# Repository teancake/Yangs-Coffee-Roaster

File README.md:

# Yangs-Coffee-Roaster
The shcematic and PCB design of the circuit board used in Yangs' Coffee Roaster.

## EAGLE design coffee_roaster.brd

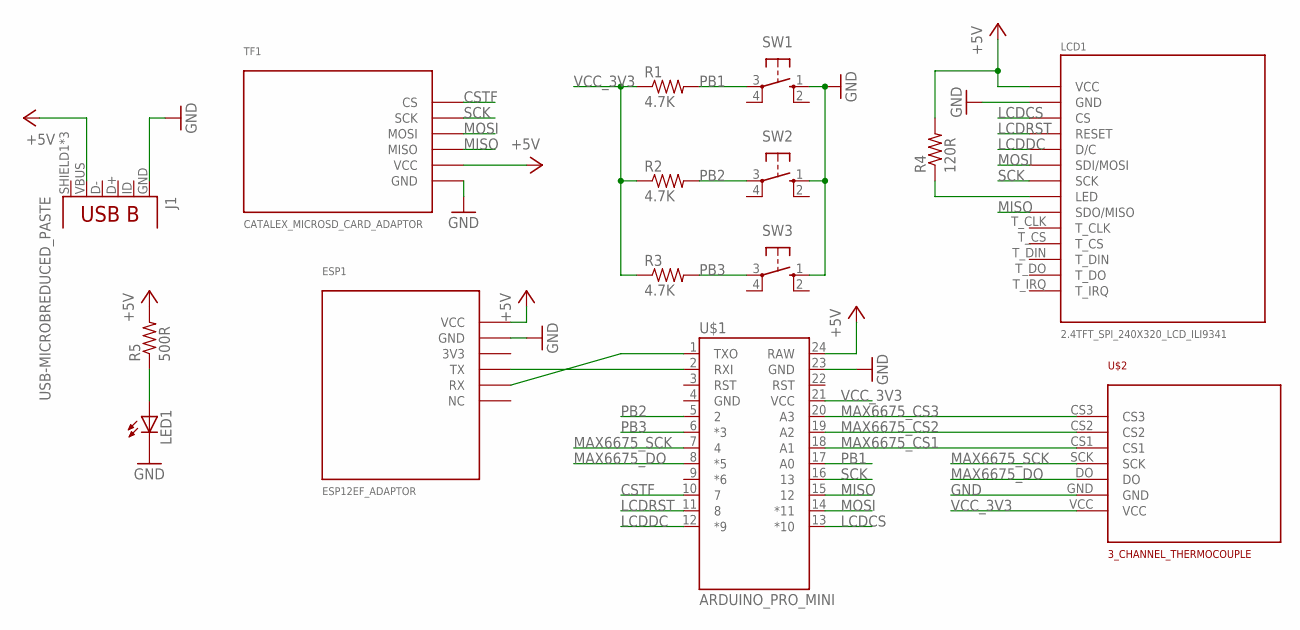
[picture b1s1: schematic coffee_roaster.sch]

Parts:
ESP1: ESP12EF_ADAPTOR
J1: USB-MICROBREDUCED_PASTE; USB-B-MICRO-SMD_V03_RED_PASTE
LCD1: 2.4TFT_SPI_240X320_LCD_ILI9341
LED1: LED5MM
R1, R2, R3: 4.7K; 0603-RES
R4: 120R; 0603-RES
R5: 500R; 0603-RES
SW1, SW2, SW3: PUSHBUTTON; B3F-10XX
TF1: CATALEX_MICROSD_CARD_ADAPTOR
U$1: ARDUINO_PRO_MINI
U$2: 3_CHANNEL_THERMOCOUPLE

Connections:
+5V: ESP1.VCC, J1.VBUS, LCD1.VCC, R4.2, R5.2, TF1.VCC, U$1.24 (RAW)
CSTF: TF1.CS, U$1.10 (7)
GND: ESP1.GND, J1.GND, LCD1.GND, LED1.K (C), SW1.1 (S), SW2.1 (S), SW3.1 (S), TF1.GND, U$1.23 (GND), U$2.GND
LCDCS: LCD1.CS, U$1.13 (*10)
LCDDC: LCD1.D/C, U$1.12 (*9)
LCDRST: LCD1.RESET, U$1.11 (8)
MAX6675_CS1: U$1.18 (A1), U$2.CS1
MAX6675_CS2: U$1.19 (A2), U$2.CS2
MAX6675_CS3: U$1.20 (A3), U$2.CS3
MAX6675_DO: U$1.8 (*5), U$2.DO
MAX6675_SCK: U$1.7 (4), U$2.SCK
MISO: LCD1.SDO/MISO, TF1.MISO, U$1.15 (12)
MOSI: LCD1.SDI/MOSI, TF1.MOSI, U$1.14 (*11)
unnamed: LCD1.LED, R4.1
unnamed: LED1.A, R5.1
unnamed: ESP1.RX, U$1.1 (TXO)
unnamed: ESP1.TX, U$1.2 (RXI)
PB1: R1.2, SW1.3, U$1.17 (A0)
PB2: R2.2, SW2.3, U$1.5 (2)
PB3: R3.2, SW3.3, U$1.6 (*3)
SCK: LCD1.SCK, TF1.SCK, U$1.16 (13)
VCC_3V3: R1.1, R2.1, R3.1, U$1.21 (VCC), U$2.VCC

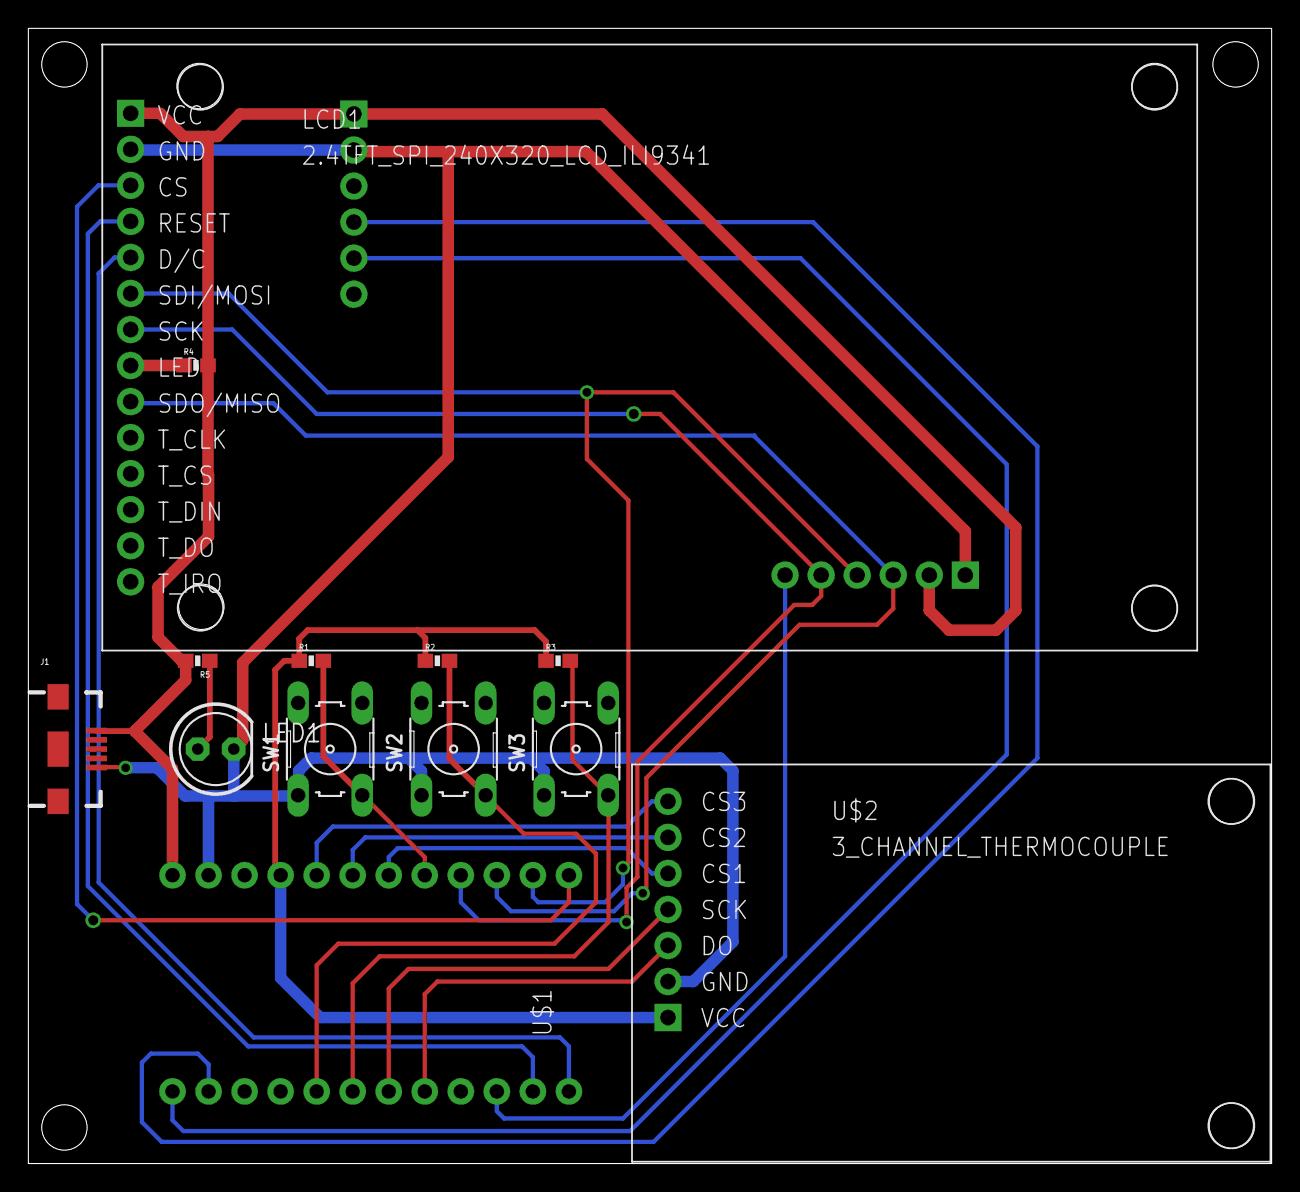
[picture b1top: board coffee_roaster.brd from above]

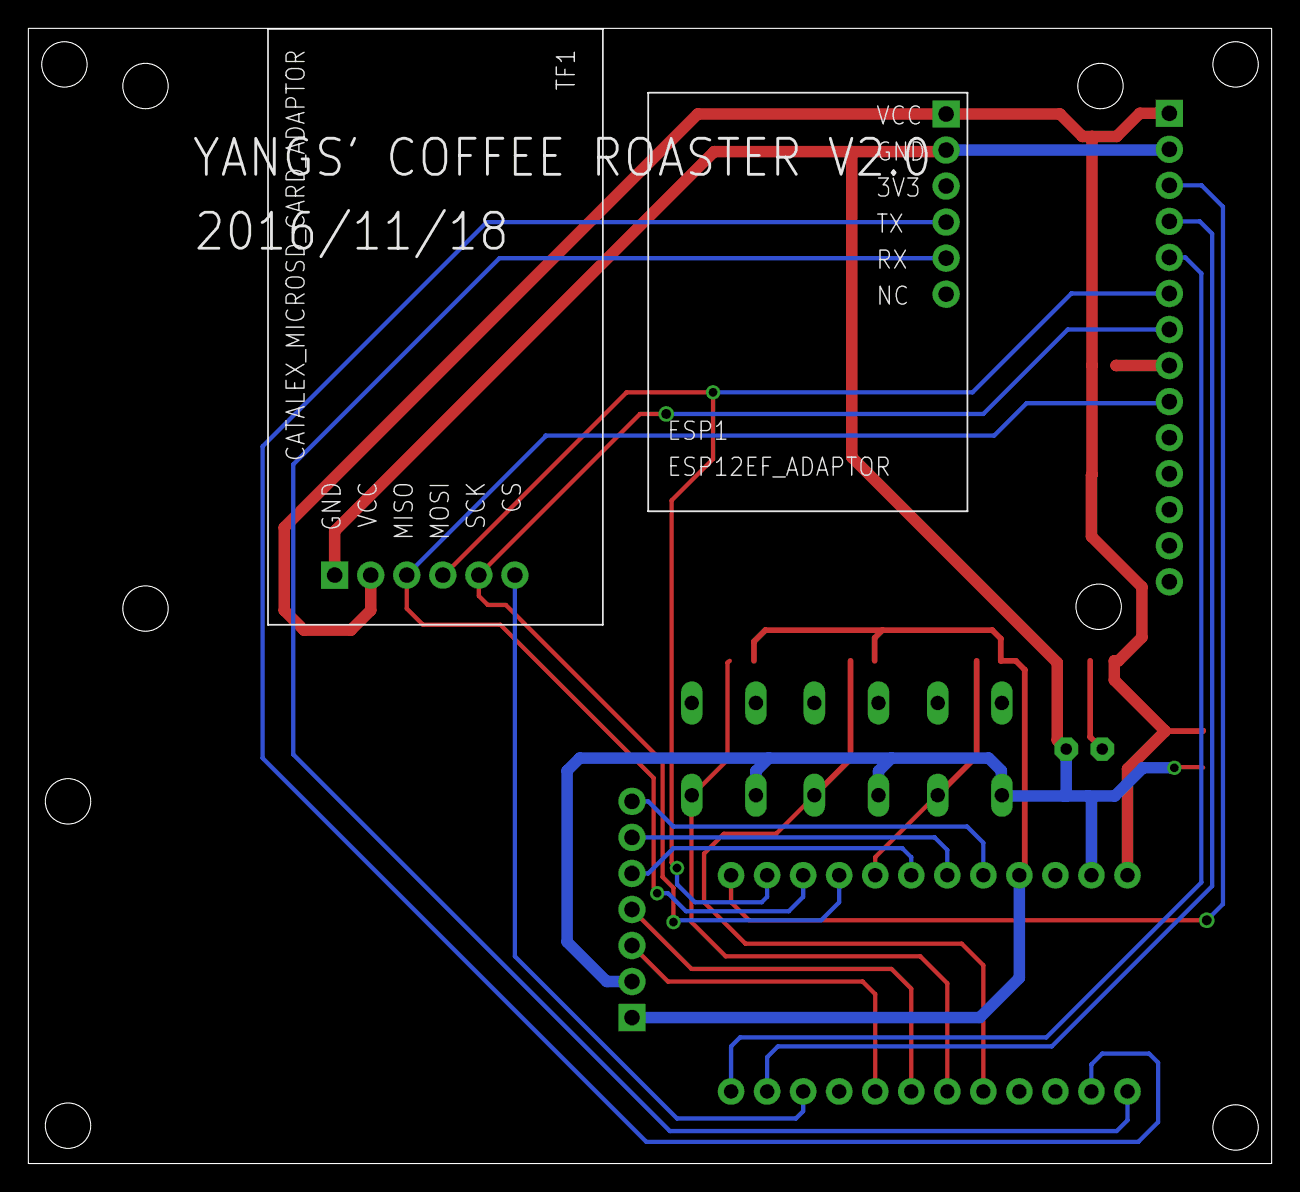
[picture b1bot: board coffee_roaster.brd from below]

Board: 2 copper layers, 87.6 x 80.0 mm, 15 parts (2 on the bottom side), 22 nets.

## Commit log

2016-12-14 all design files
2017-02-17 Add CAD files for the 3D printed case and a tiny update of the readme file.
2017-02-17 Add CAD files for the 3D printed case.
